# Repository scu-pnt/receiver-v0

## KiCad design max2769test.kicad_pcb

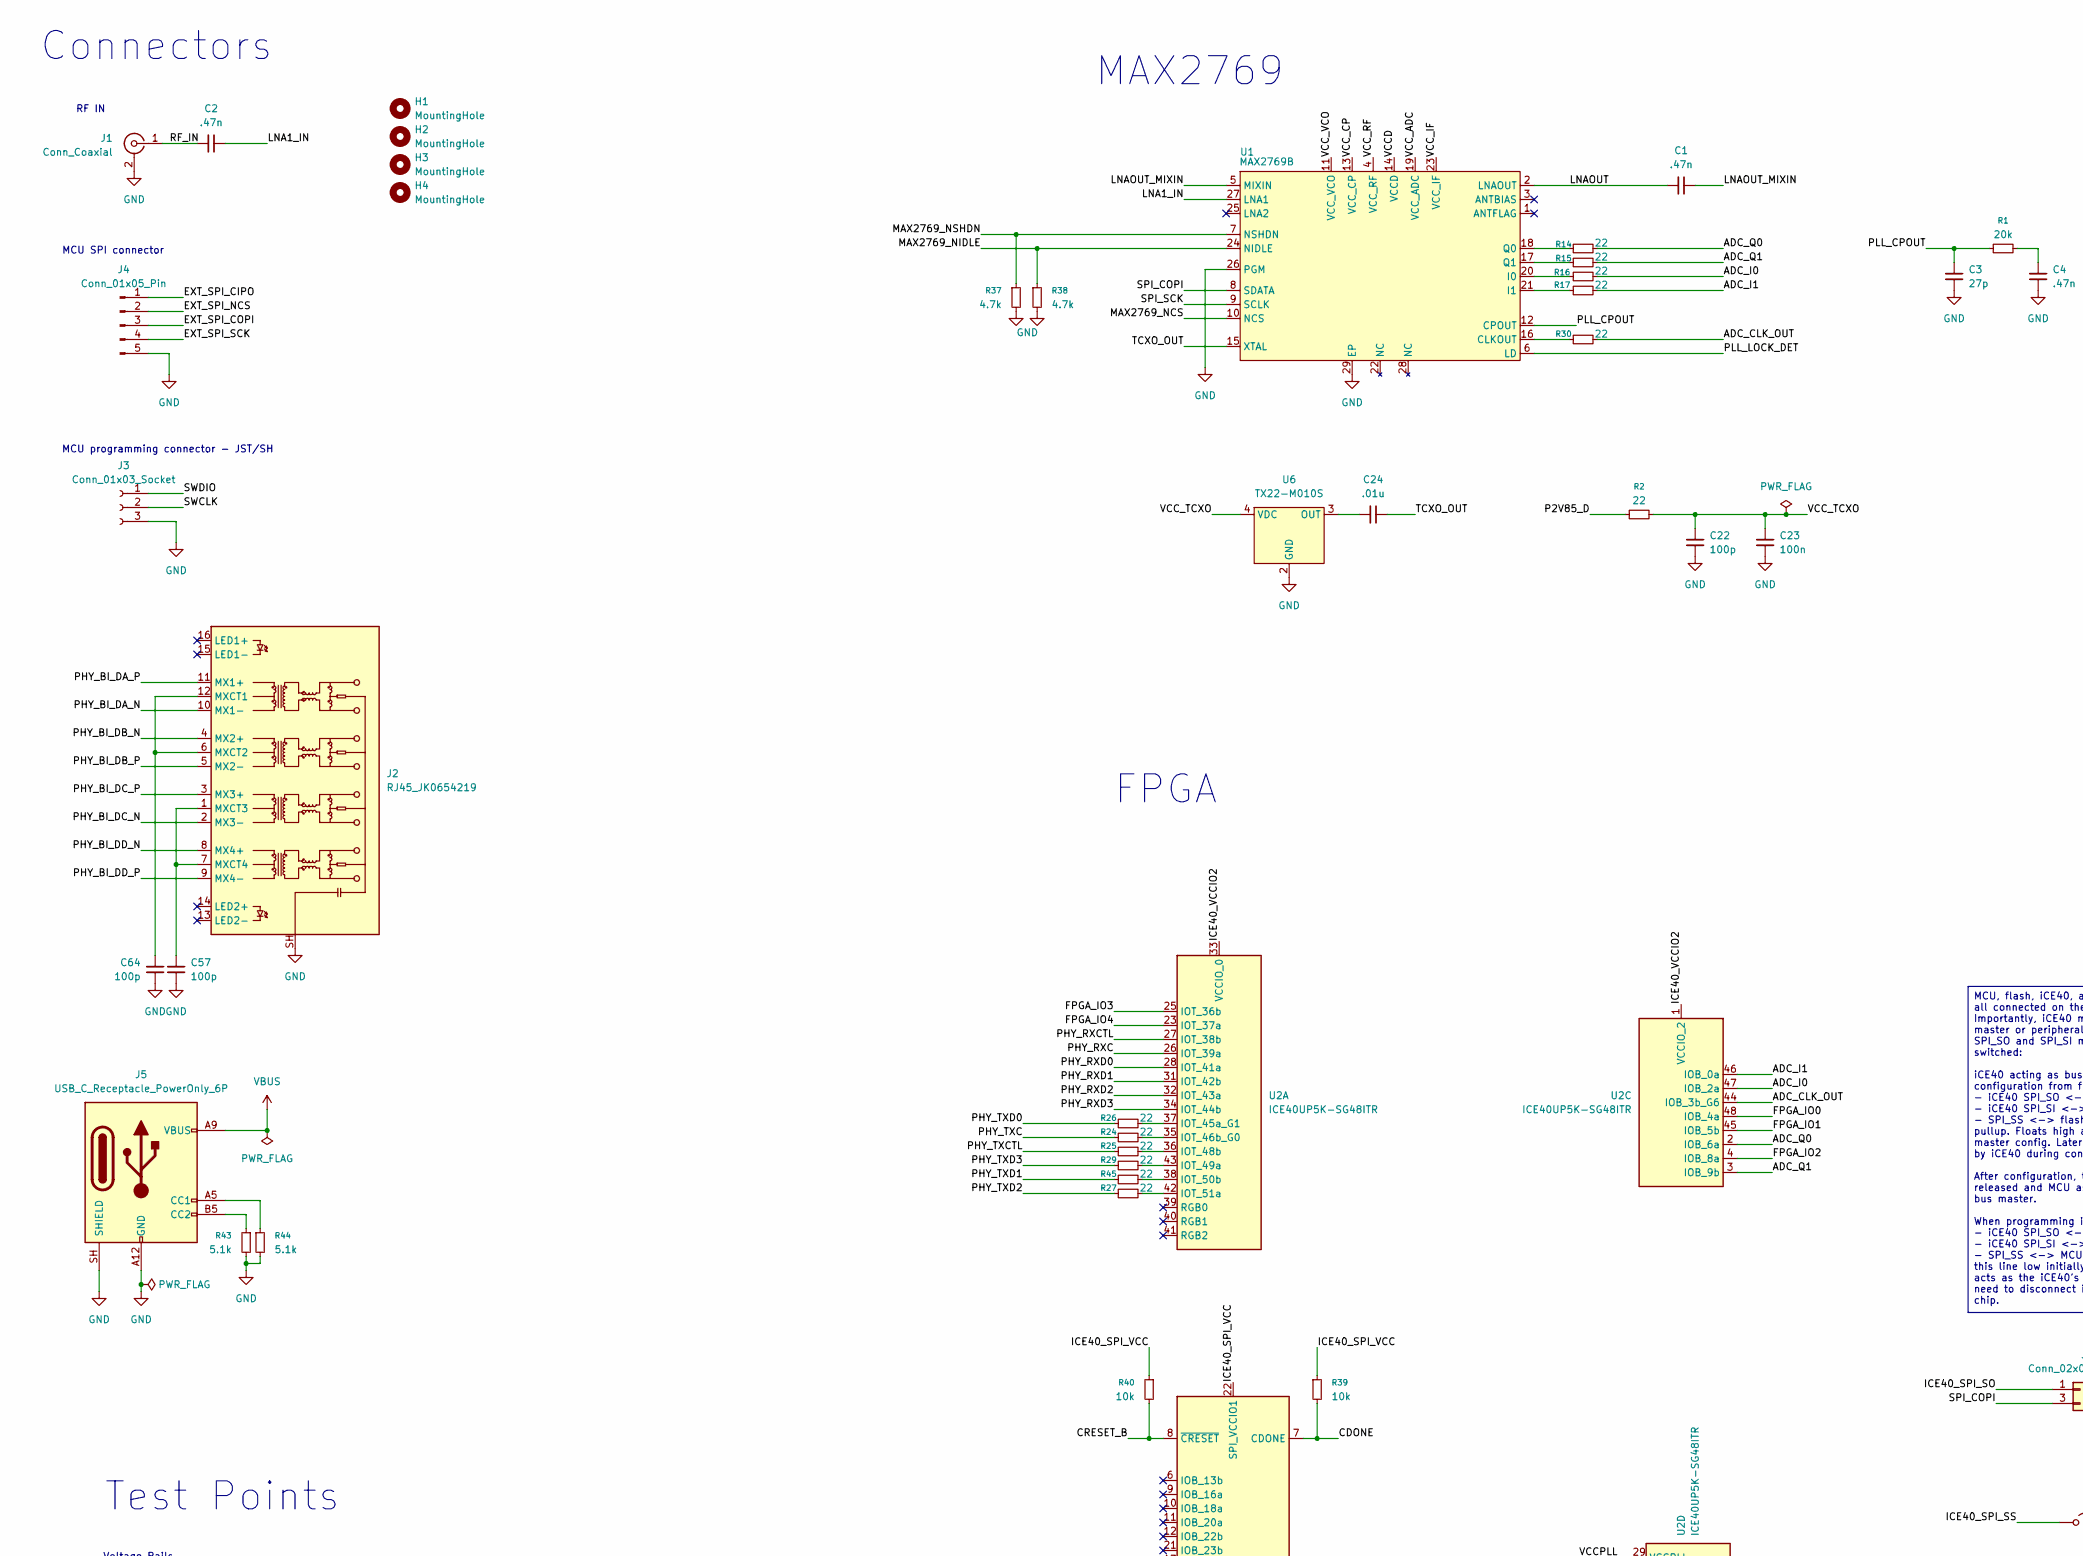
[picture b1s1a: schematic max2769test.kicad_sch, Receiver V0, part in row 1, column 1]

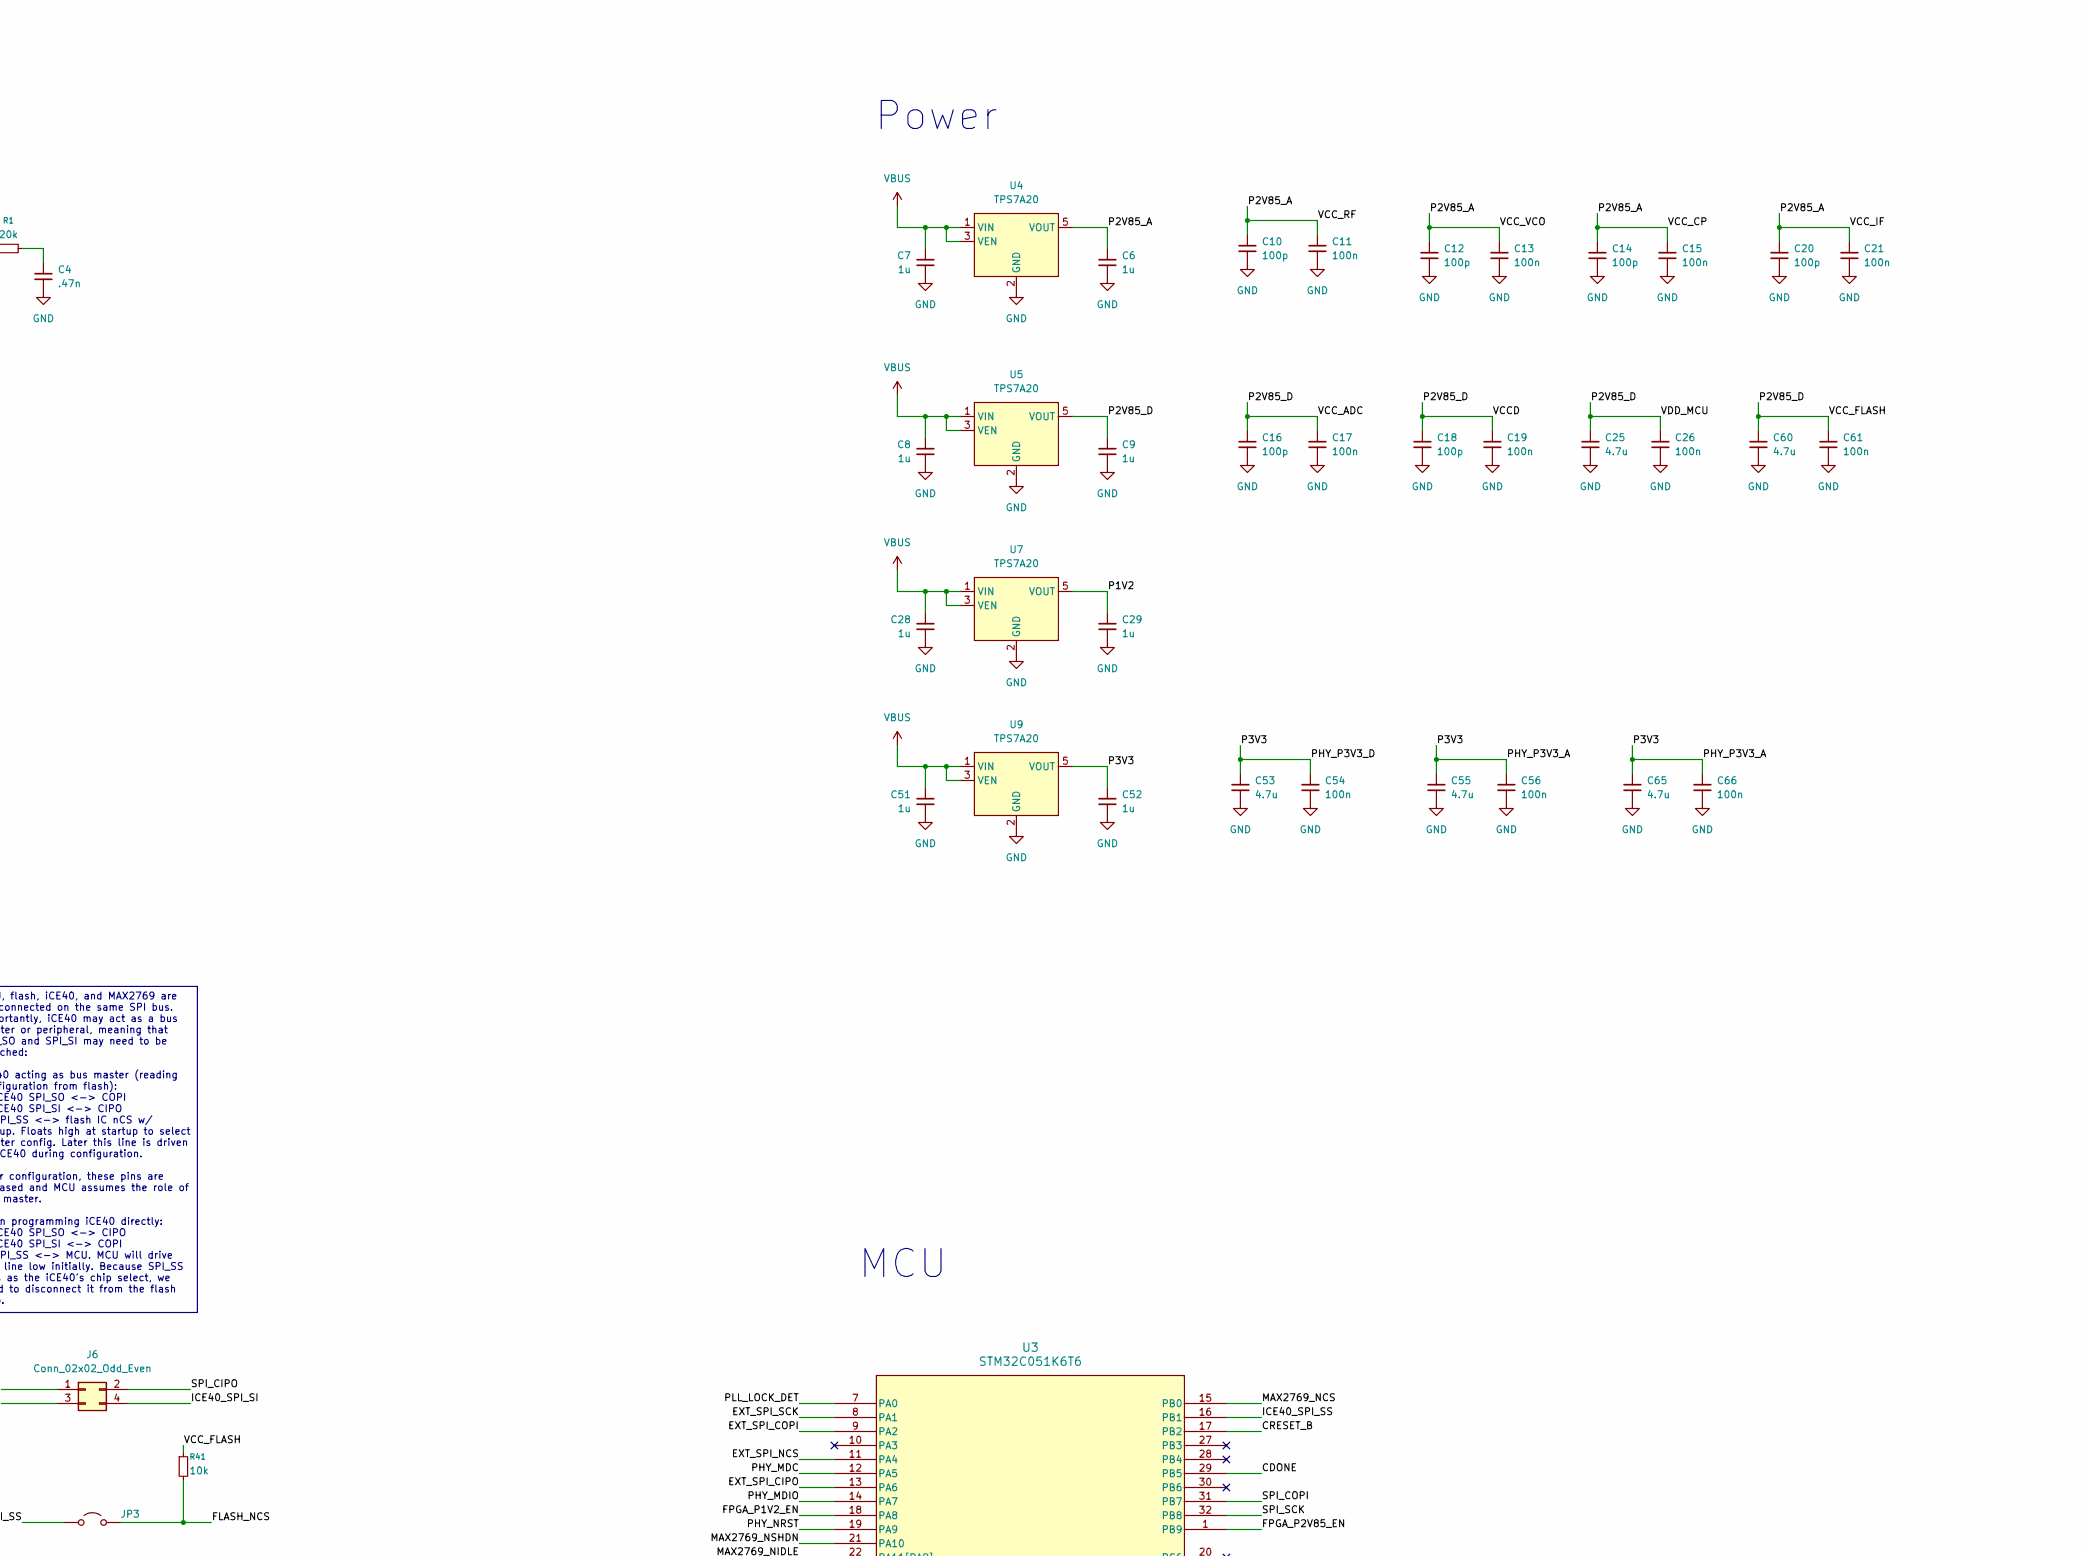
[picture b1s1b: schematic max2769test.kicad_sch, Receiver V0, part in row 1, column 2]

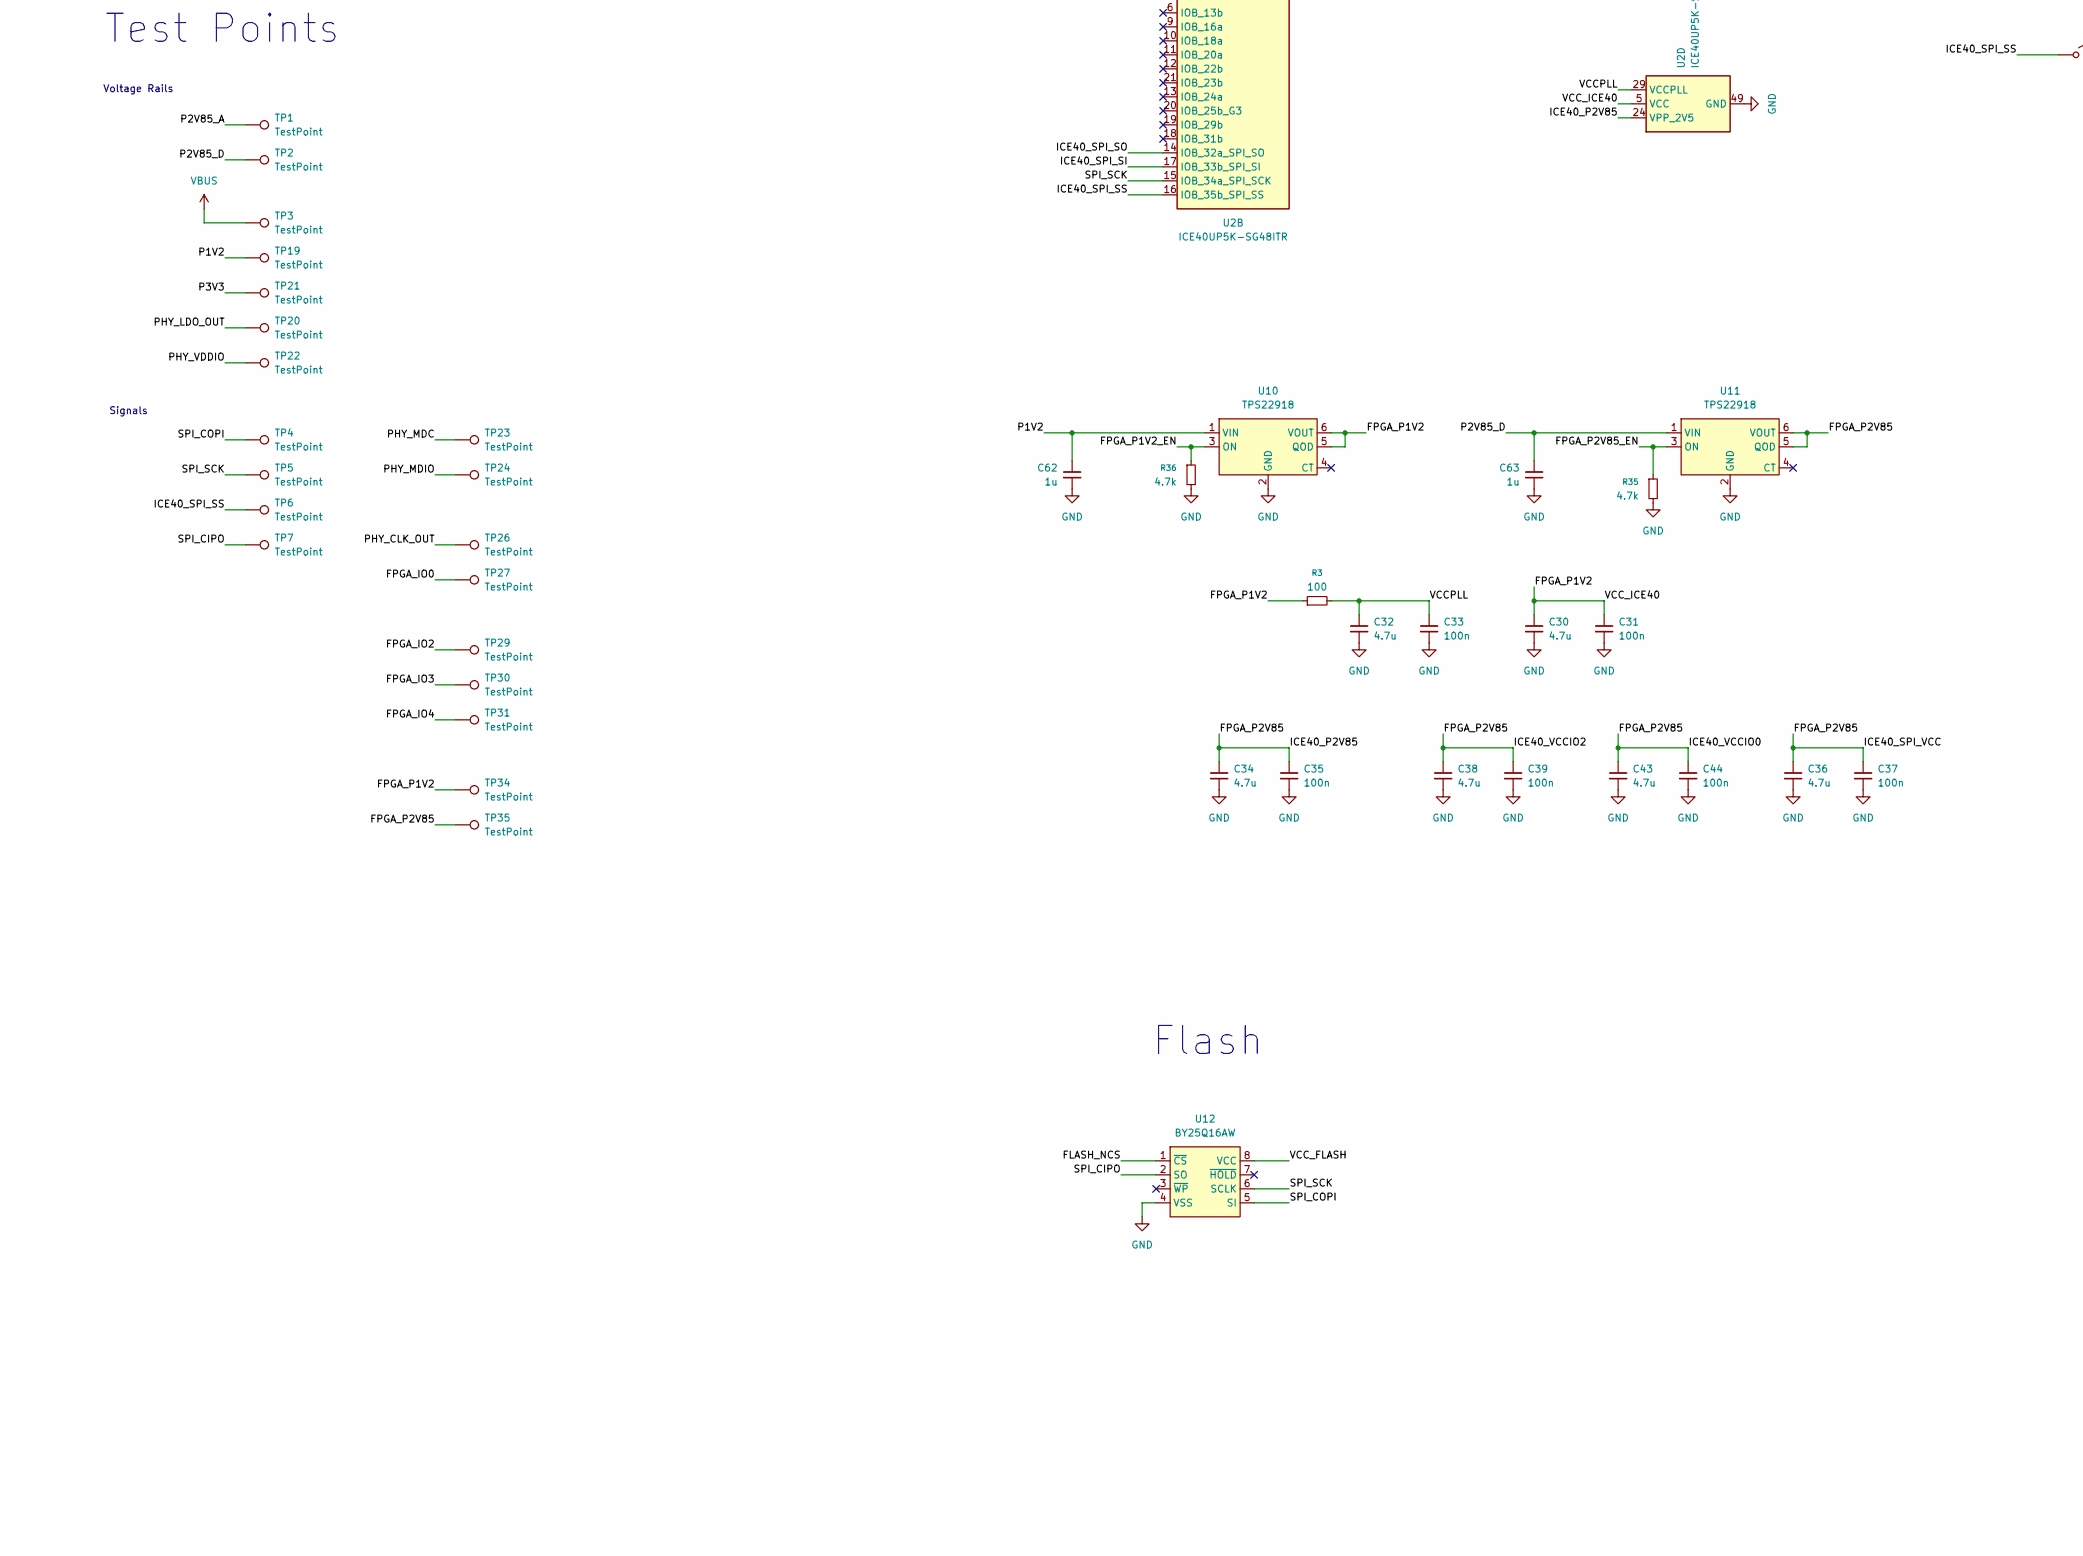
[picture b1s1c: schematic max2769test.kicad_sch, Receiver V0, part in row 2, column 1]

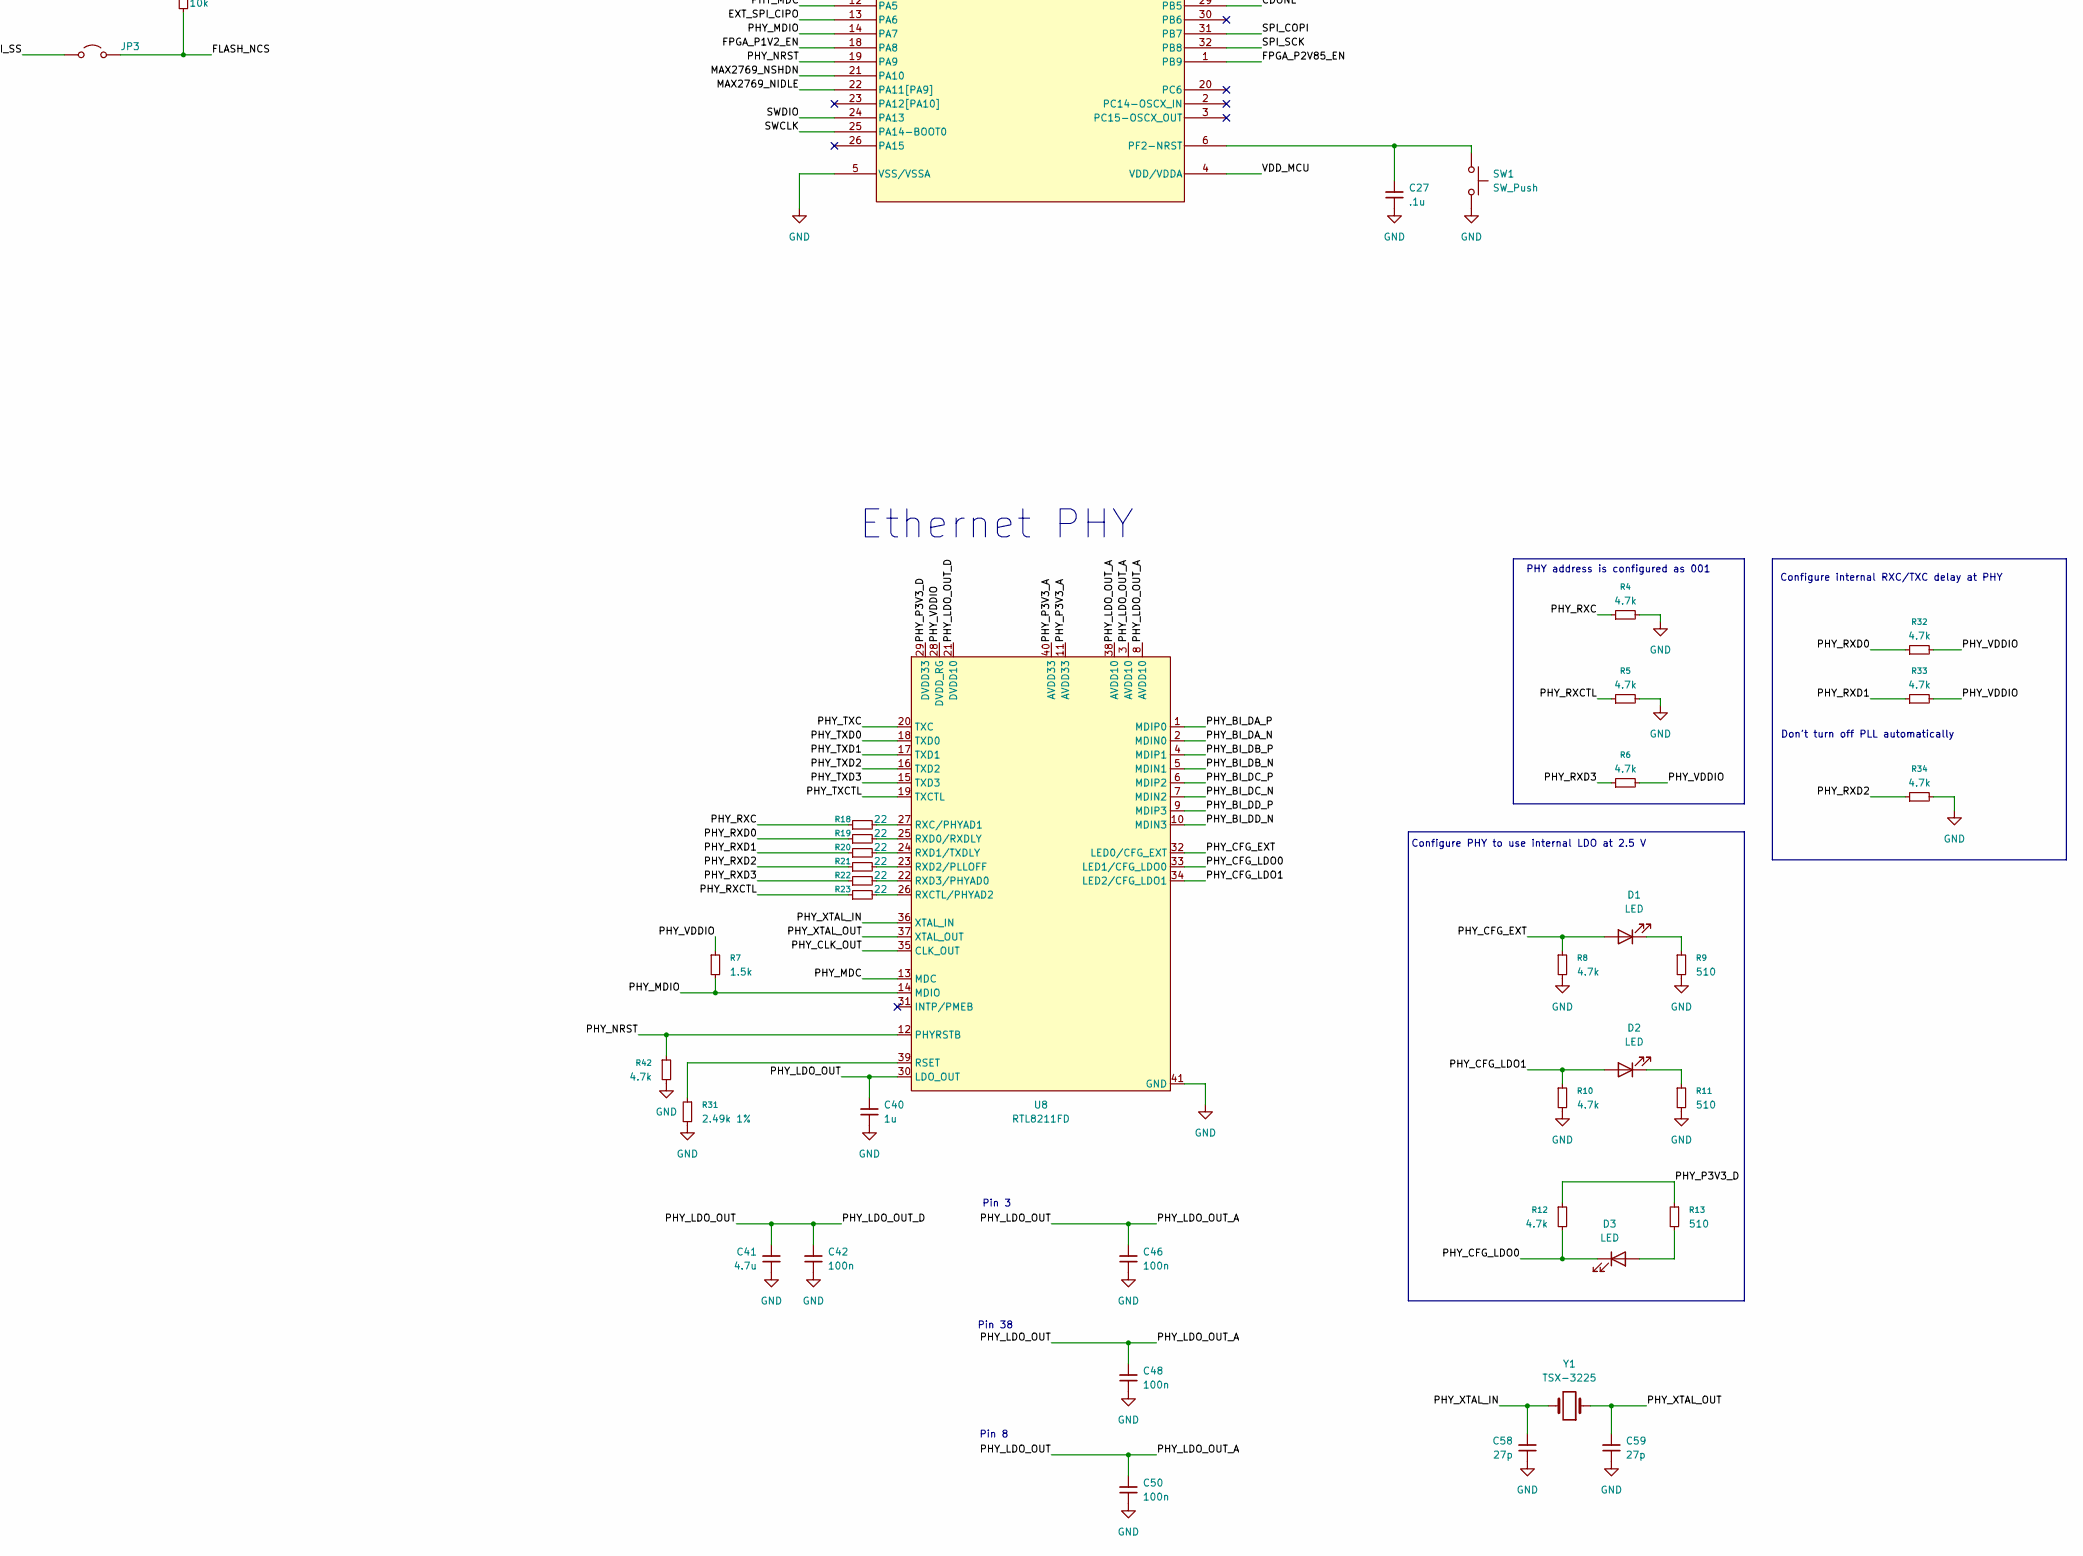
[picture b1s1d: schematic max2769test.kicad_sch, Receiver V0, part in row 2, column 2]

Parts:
C1, C2, C4: .47n; C_0402_1005Metric
C3, C58, C59: 27p; C_0402_1005Metric
C6, C7, C8, C9, C28, C29, C51, C52, C62, C63: 1u; C_0603_1608Metric
C10, C12, C14, C16, C18: 100p; C_0402_1005Metric
C11, C13, C15, C17, C19, C31, C33, C35, C37, C39, C42, C44, C46, C48, C50, C54, C56, C66: 100n; C_0402_1005Metric
C20, C22, C57, C64: 100p; C_0603_1608Metric
C21, C23, C26, C61: 100n; C_0603_1608Metric
C24: .01u; C_0402_1005Metric
C25, C60: 4.7u; C_0603_1608Metric
C27: .1u; C_0603_1608Metric
C30, C32, C34, C36, C38, C41, C43, C53, C55, C65: 4.7u; C_0402_1005Metric
C40: 1u; C_0402_1005Metric
D1, D2, D3: LED; LED_0805_2012Metric
H1, H2, H3, H4: MountingHole; MountingHole_3.2mm_M3
J1: Conn_Coaxial; SMA_Samtec_SMA-J-P-H-ST-EM1_EdgeMount
J2: RJ45_JK0654219; RJ45_Pulse_JK0654219NL_Horizontal
J3: Conn_01x03_Socket; JST_SH_SM03B-SRSS-TB_1x03-1MP_P1.00mm_Horizontal
J4: Conn_01x05_Pin; PinHeader_1x05_P2.54mm_Vertical
J5: USB_C_Receptacle_PowerOnly_6P; USB_C_Receptacle_GCT_USB4125-xx-x_6P_TopMnt_Horizontal
J6: Conn_02x02_Odd_Even; PinHeader_2x02_P2.54mm_Vertical
JP3: Jumper_2_Open; PinHeader_1x02_P2.54mm_Vertical
R1: 20k; R_0402_1005Metric
R2: 22; R_0603_1608Metric
R3: 100; R_0402_1005Metric
R4, R8, R10, R12, R35, R36, R37, R38, R42: 4.7k; R_0603_1608Metric
R5, R6, R32, R33, R34: 4.7k; R_0402_1005Metric
R7: 1.5k; R_0603_1608Metric
R9, R11, R13: 510; R_0603_1608Metric
R14, R15, R16, R17, R18, R19, R20, R21, R22, R23, R24, R25, R26, R27, R29, R30, R45: 22; R_0402_1005Metric
R31: 2.49k 1%; R_0603_1608Metric
R39, R40, R41: 10k; R_0603_1608Metric
R43, R44: 5.1k; R_0603_1608Metric
SW1: SW_Push; SW_PUSH_6mm
TP1, TP2, TP3, TP4, TP5, TP6, TP7, TP19, TP20, TP21, TP22, TP23, TP24, TP26, TP27, TP29, TP30, TP31, TP34, TP35: TestPoint; TestPoint_Pad_D1.0mm
U1: MAX2769B; TQFN-28-1EP_5x5mm_P0.5mm_EP3.25x3.25mm_ThermalVias
U2: ICE40UP5K-SG48ITR; QFN-48-1EP_7x7mm_P0.5mm_EP5.6x5.6mm_ThermalVias
U3: STM32C051K6T6; LQFP-32_7x7mm_P0.8mm
U4, U5, U7, U9: TPS7A20; SOT-23-5
U6: TX22-M010S; Crystal_SMD_WE_CFPX-218-4Pin_2.5x2.0mm
U8: RTL8211FD; QFN-40-1EP_5x5mm_P0.4mm_EP3.6x3.6mm_ThermalVias
U10, U11: TPS22918; SOT-23-6
U12: BY25Q16AW; SOIC-8_3.9x4.9mm_P1.27mm
Y1: TSX-3225; Crystal_SMD_3225-4Pin_3.2x2.5mm

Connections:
/ADC_CLK_OUT: R30.2, U2.44 (IOB_3b_G6)
/ADC_I0: R16.2, U2.47 (IOB_2a)
/ADC_I1: R17.2, U2.46 (IOB_0a)
/ADC_Q0: R14.2, U2.2 (IOB_6a)
/ADC_Q1: R15.2, U2.3 (IOB_9b)
/CDONE: R39.2, U2.7 (CDONE), U3.29 (PB5)
/CRESET_B: R40.2, U2.8 (~CRESET), U3.17 (PB2)
/EXT_SPI_CIPO: J4.1, U3.13 (PA6)
/EXT_SPI_COPI: J4.3, U3.9 (PA2)
/EXT_SPI_NCS: J4.2, U3.11 (PA4)
/EXT_SPI_SCK: J4.4, U3.8 (PA1)
/FLASH_NCS: JP3.2 (B), R41.2, U12.1 (~CS)
/FPGA_IO0: TP27.1 (1_1), U2.48 (IOB_4a)
/FPGA_IO1: U2.45 (IOB_5b)
/FPGA_IO2: TP29.1 (1_1), U2.4 (IOB_8a)
/FPGA_IO3: TP30.1 (1_1), U2.25 (IOT_36b)
/FPGA_IO4: TP31.1 (1_1), U2.23 (IOT_37a)
/FPGA_P1V2: C30.1, C31.1, R3.1, TP34.1 (1_1), U2.5 (VCC), U2.30 (VCC), U10.5 (QOD), U10.6 (VOUT)
/FPGA_P1V2_EN: R36.1, U3.18 (PA8), U10.3 (ON)
/FPGA_P2V85: C34.1, C35.1, C36.1, C37.1, C38.1, C39.1, C43.1, C44.1, R39.1, R40.1, TP35.1 (1_1), U2.1 (VCCIO_2), U2.22 (SPI_VCCIO1), U2.24 (VPP_2V5), U2.33 (VCCIO_0), U11.5 (QOD), U11.6 (VOUT)
/FPGA_P2V85_EN: R35.1, U3.1 (PB9), U11.3 (ON)
/ICE40_SPI_SI: J6.4, U2.17 (IOB_33b_SPI_SI)
/ICE40_SPI_SO: J6.1, U2.14 (IOB_32a_SPI_SO)
/ICE40_SPI_SS: JP3.1 (A), TP6.1 (1_1), U2.16 (IOB_35b_SPI_SS), U3.16 (PB1)
/LNA1_IN: C2.2, U1.27 (LNA1)
/LNAOUT: C1.1, U1.2 (LNAOUT)
/LNAOUT_MIXIN: C1.2, U1.5 (MIXIN)
/MAX2769_NCS: U1.10 (NCS), U3.15 (PB0)
/MAX2769_NIDLE: R38.1, U1.24 (NIDLE), U3.22 (PA11[PA9])
/MAX2769_NSHDN: R37.1, U1.7 (NSHDN), U3.21 (PA10)
/P1V2: C29.1, C62.1, TP19.1 (1_1), U7.5 (VOUT), U10.1 (VIN)
/P2V85_A: C6.1, C10.1, C11.1, C12.1, C13.1, C14.1, C15.1, C20.1, C21.1, TP1.1 (1_1), U1.4 (VCC_RF), U1.11 (VCC_VCO), U1.13 (VCC_CP), U1.23 (VCC_IF), U4.5 (VOUT)
/P2V85_D: C9.1, C16.1, C17.1, C18.1, C19.1, C25.1, C26.1, C60.1, C61.1, C63.1, R2.1, R41.1, TP2.1 (1_1), U1.14 (VCCD), U1.19 (VCC_ADC), U3.4 (VDD/VDDA), U5.5 (VOUT), U11.1 (VIN), U12.8 (VCC)
/P3V3: C52.1, C53.1, C54.1, C55.1, C56.1, C65.1, C66.1, R12.1, R13.1, TP21.1 (1_1), U8.11 (AVDD33), U8.29 (DVDD33), U8.40 (AVDD33), U9.5 (VOUT)
/PHY_BI_DA_N: J2.10 (MX1-), U8.2 (MDIN0)
/PHY_BI_DA_P: J2.11 (MX1+), U8.1 (MDIP0)
/PHY_BI_DB_N: J2.4 (MX2+), U8.5 (MDIN1)
/PHY_BI_DB_P: J2.5 (MX2-), U8.4 (MDIP1)
/PHY_BI_DC_N: J2.2 (MX3-), U8.7 (MDIN2)
/PHY_BI_DC_P: J2.3 (MX3+), U8.6 (MDIP2)
/PHY_BI_DD_N: J2.8 (MX4+), U8.10 (MDIN3)
/PHY_BI_DD_P: J2.9 (MX4-), U8.9 (MDIP3)
/PHY_CFG_EXT: D1.2 (A), R8.1, U8.32 (LED0/CFG_EXT)
/PHY_CFG_LDO0: D3.1 (K), R12.2, U8.33 (LED1/CFG_LDO0)
/PHY_CFG_LDO1: D2.2 (A), R10.1, U8.34 (LED2/CFG_LDO1)
/PHY_CLK_OUT: TP26.1 (1_1), U8.35 (CLK_OUT)
/PHY_LDO_OUT: C40.1, C41.1, C42.1, C46.1, C48.1, C50.1, TP20.1 (1_1), U8.3 (AVDD10), U8.8 (AVDD10), U8.21 (DVDD10), U8.30 (LDO_OUT), U8.38 (AVDD10)
/PHY_MDC: TP23.1 (1_1), U3.12 (PA5), U8.13 (MDC)
/PHY_MDIO: R7.2, TP24.1 (1_1), U3.14 (PA7), U8.14 (MDIO)
/PHY_NRST: R42.1, U3.19 (PA9), U8.12 (PHYRSTB)
/PHY_RXC: R4.1, R18.1, U2.26 (IOT_39a)
/PHY_RXCTL: R5.1, R23.1, U2.27 (IOT_38b)
/PHY_RXD0: R19.1, R32.1, U2.28 (IOT_41a)
/PHY_RXD1: R20.1, R33.1, U2.31 (IOT_42b)
/PHY_RXD2: R21.1, R34.1, U2.32 (IOT_43a)
/PHY_RXD3: R6.1, R22.1, U2.34 (IOT_44b)
/PHY_TXC: R24.1, U8.20 (TXC)
/PHY_TXCTL: R25.1, U8.19 (TXCTL)
/PHY_TXD0: R26.1, U8.18 (TXD0)
/PHY_TXD1: R45.1, U8.17 (TXD1)
/PHY_TXD2: R27.1, U8.16 (TXD2)
/PHY_TXD3: R29.1, U8.15 (TXD3)
/PHY_VDDIO: R6.2, R7.1, R32.2, R33.2, TP22.1 (1_1), U8.28 (DVDD_RG)
/PHY_XTAL_IN: C58.1, U8.36 (XTAL_IN), Y1.2
/PHY_XTAL_OUT: C59.1, U8.37 (XTAL_OUT), Y1.1
/PLL_CPOUT: C3.1, R1.1, U1.12 (CPOUT)
/PLL_LOCK_DET: U1.6 (LD), U3.7 (PA0)
/RF_IN: C2.1, J1.1 (In)
/SPI_CIPO: J6.2, TP7.1 (1_1), U12.2 (SO)
/SPI_COPI: J6.3, TP4.1 (1_1), U1.8 (SDATA), U3.31 (PB7), U12.5 (SI)
/SPI_SCK: TP5.1 (1_1), U1.9 (SCLK), U2.15 (IOB_34a_SPI_SCK), U3.32 (PB8), U12.6 (SCLK)
/SWCLK: J3.2, U3.25 (PA14-BOOT0)
/SWDIO: J3.1, U3.24 (PA13)
/TCXO_OUT: C24.2, U1.15 (XTAL)
/VCCPLL: C32.1, C33.1, R3.2, U2.29 (VCCPLL)
/VCC_TCXO: C22.1, C23.1, R2.2, U6.4 (VDC)
GND: C3.2, C4.2, C6.2, C7.2, C8.2, C9.2, C10.2, C11.2, C12.2, C13.2, C14.2, C15.2, C16.2, C17.2, C18.2, C19.2, C20.2, C21.2, C22.2, C23.2, C25.2, C26.2, C27.2, C28.2, C29.2, C30.2, C31.2, C32.2, C33.2, C34.2, C35.2, C36.2, C37.2, C38.2, C39.2, C40.2, C41.2, C42.2, C43.2, C44.2, C46.2, C48.2, C50.2, C51.2, C52.2, C53.2, C54.2, C55.2, C56.2, C57.2, C58.2, C59.2, C60.2, C61.2, C62.2, C63.2, C64.2, C65.2, C66.2, J1.2 (Ext), J2.SH, J3.3, J4.5, J5.A12 (GND), J5.B12 (GND), J5.SH (SHIELD), R4.2, R5.2, R8.2, R9.2, R10.2, R11.2, R31.2, R34.2, R35.2, R36.2, R37.2, R38.2, R42.2, R43.2, R44.2, SW1.2, U1.26 (PGM), U1.29 (EP), U2.49 (GND), U3.5 (VSS/VSSA), U4.2 (GND), U5.2 (GND), U6.2 (GND), U7.2 (GND), U8.41 (GND), U9.2 (GND), U10.2 (GND), U11.2 (GND), U12.4 (VSS)
unnamed: C4.1, R1.2
unnamed: D1.1 (K), R9.1
unnamed: D2.1 (K), R11.1
unnamed: D3.2 (A), R13.2
unnamed: C64.1, J2.6 (MXCT2), J2.12 (MXCT1)
unnamed: C57.1, J2.1 (MXCT3), J2.7 (MXCT4)
unnamed: J5.A5 (CC1), R44.1
unnamed: J5.B5 (CC2), R43.1
unnamed: R30.1, U1.16 (CLKOUT)
unnamed: R16.1, U1.20 (I0)
unnamed: R17.1, U1.21 (I1)
unnamed: R14.1, U1.18 (Q0)
unnamed: R15.1, U1.17 (Q1)
unnamed: R26.2, U2.37 (IOT_45a_G1)
unnamed: R24.2, U2.35 (IOT_46b_G0)
unnamed: R25.2, U2.36 (IOT_48b)
unnamed: R29.2, U2.43 (IOT_49a)
unnamed: R45.2, U2.38 (IOT_50b)
unnamed: R27.2, U2.42 (IOT_51a)
unnamed: C27.1, SW1.1, U3.6 (PF2-NRST)
unnamed: C24.1, U6.3 (OUT)
unnamed: R31.1, U8.39 (RSET)
unnamed: R23.2, U8.26 (RXCTL/PHYAD2)
unnamed: R18.2, U8.27 (RXC/PHYAD1)
unnamed: R19.2, U8.25 (RXD0/RXDLY)
unnamed: R20.2, U8.24 (RXD1/TXDLY)
unnamed: R21.2, U8.23 (RXD2/PLLOFF)
unnamed: R22.2, U8.22 (RXD3/PHYAD0)
VBUS: C7.1, C8.1, C28.1, C51.1, J5.A9 (VBUS), J5.B9 (VBUS), TP3.1 (1_1), U4.1 (VIN), U4.3 (VEN), U5.1 (VIN), U5.3 (VEN), U7.1 (VIN), U7.3 (VEN), U9.1 (VIN), U9.3 (VEN)

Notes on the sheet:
Don't turn off PLL automatically
MCU programming connector - JST/SH
Configure PHY to use internal LDO at 2.5 V
Ethernet PHY
Configure internal RXC/TXC delay at PHY
Voltage Rails
Pin 3
Connectors
RF IN
PHY address is configured as 001
MCU
Pin 38
Test Points
MCU SPI connector
Pin 8
FPGA
Power
MAX2769
Signals
Flash
MCU, flash, iCE40, and MAX2769 are all connected on the same SPI bus. Importantly, iCE40 may act as a bus master or peripheral, meaning that SPI_SO and SPI_SI may need to be switched: iCE40 acting as bus master (reading configuration from flash): - iCE40 SPI_SO <-> COPI - iCE40 SPI_SI <-> CIPO - SP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

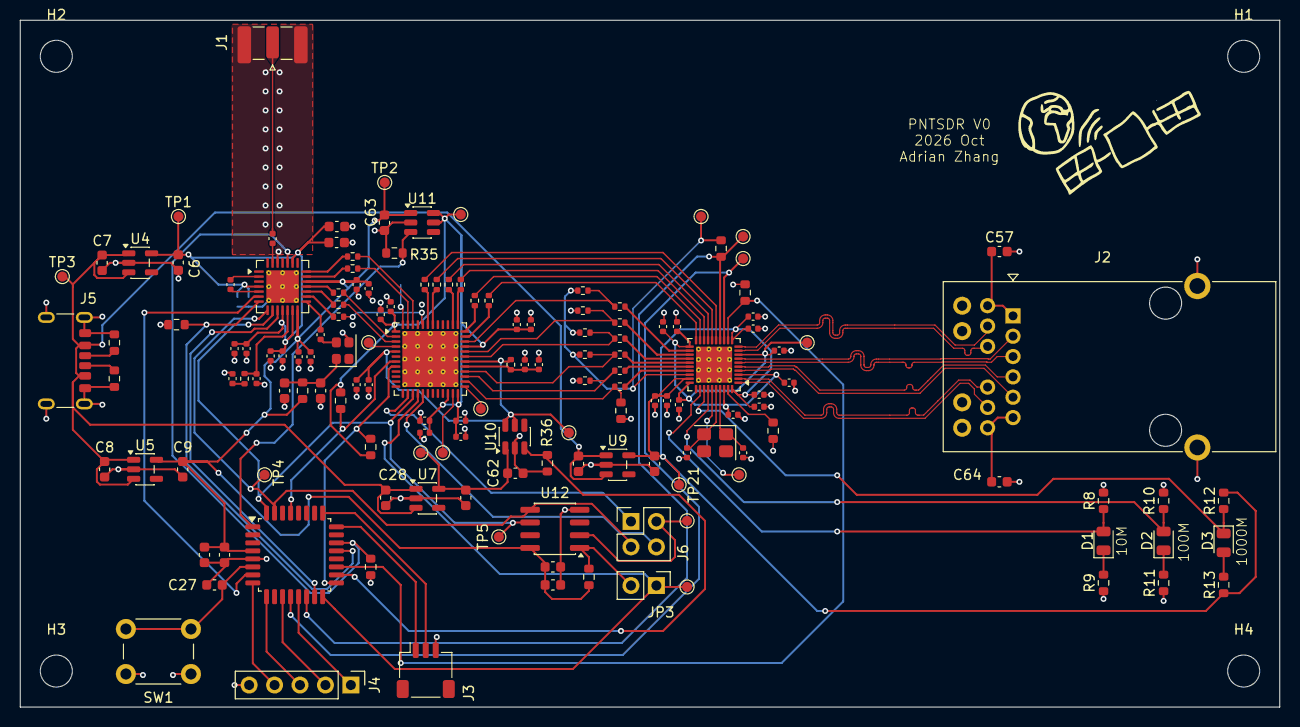
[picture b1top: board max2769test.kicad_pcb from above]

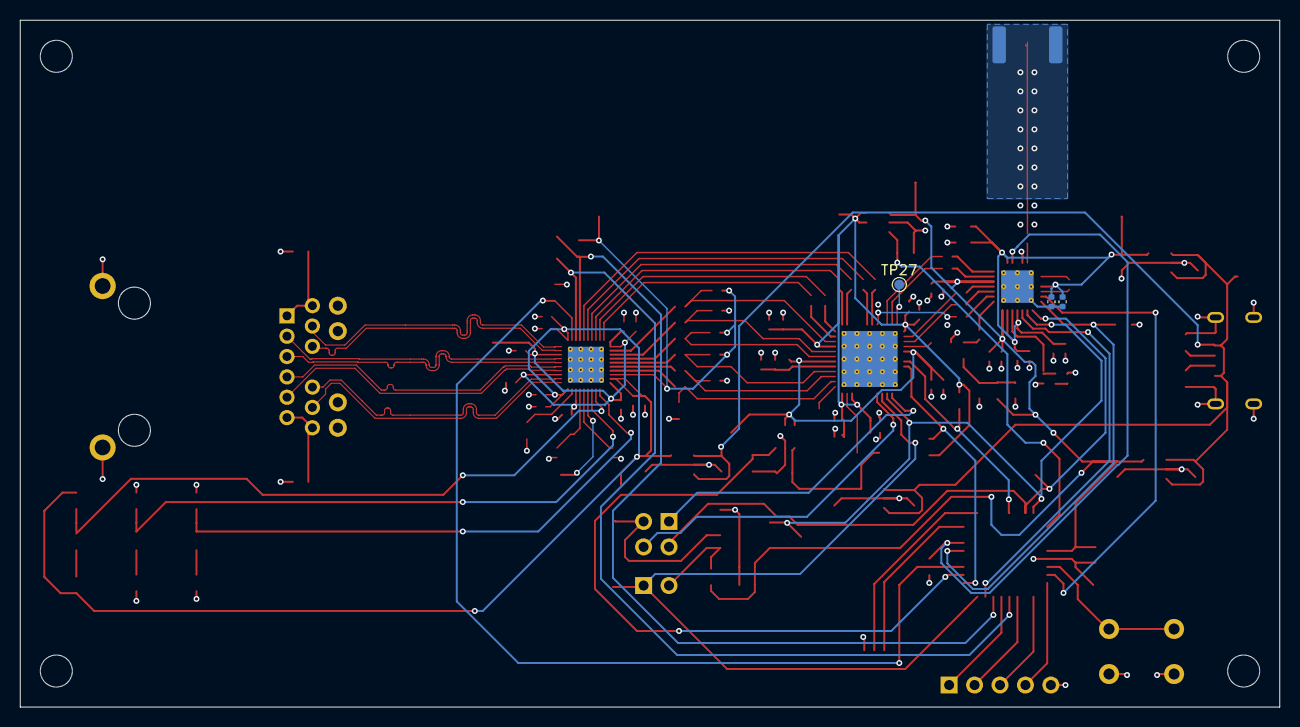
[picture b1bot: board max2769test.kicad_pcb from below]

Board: 4 copper layers, 125.8 x 68.6 mm, 154 parts (3 on the bottom side), 105 nets.
